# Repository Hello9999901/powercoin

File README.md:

# powercoin

Powercoin is an ultra-compact Qi-certified wireless power transfer receiver. A functional prototype was achieved in May 2022, and full integration into devices like the Logitech G502 or similar Razer products are planned. Optimized for production with JLCPCB.

> _Blender animated render of the powercoin (EEVEE rendering engine, custom procedural materials)_

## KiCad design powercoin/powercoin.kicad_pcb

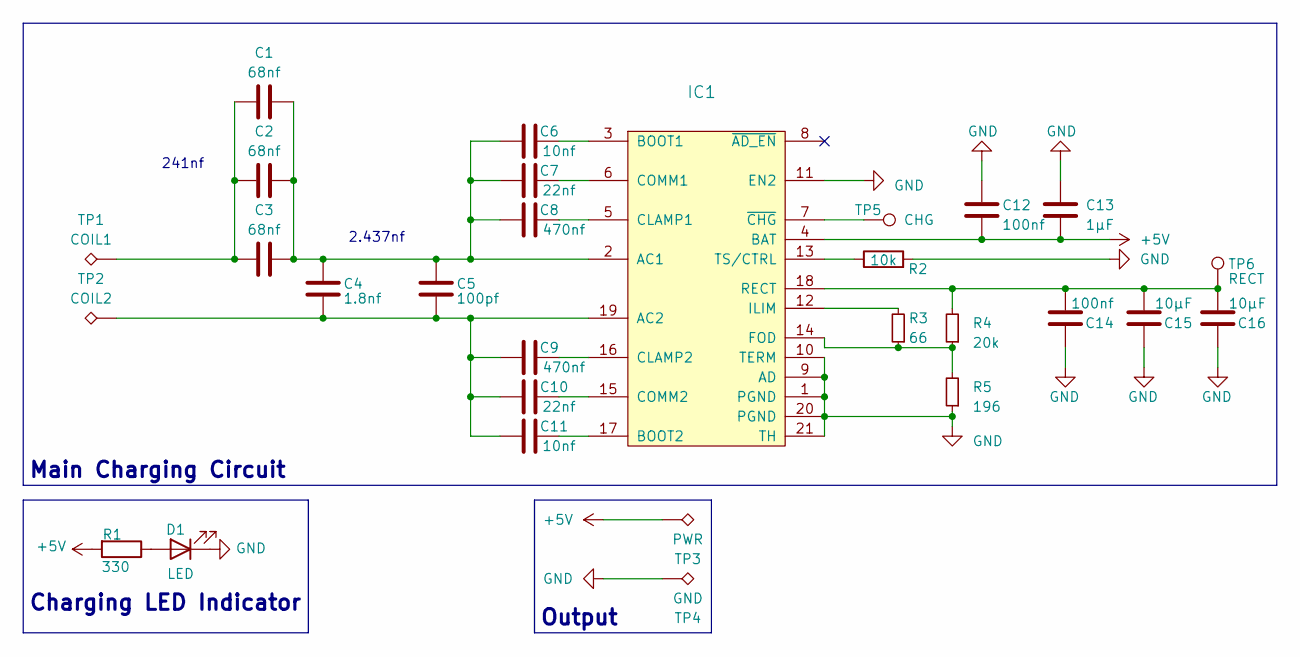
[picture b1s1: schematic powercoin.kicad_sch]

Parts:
C1, C2, C3: 68nf; C_0603_1608Metric; LCSC C107098
C4: 1.8nf; C_0603_1608Metric; LCSC C318642
C5: 100pf; C_0603_1608Metric; LCSC C14858
C6, C11: 10nf; C_0603_1608Metric; LCSC C100042
C7, C10: 22nf; C_0603_1608Metric; LCSC C21122
C8, C9: 470nf; C_0603_1608Metric; LCSC C1620
C12, C14: 100nf; C_0603_1608Metric; LCSC C14663
C13: 1μF; C_0603_1608Metric; LCSC C1592
C15, C16: 10μF; C_0603_1608Metric; LCSC C85713
D1: LED; LED_0805_2012Metric; LCSC C965818
IC1: Texas_VQFN-RHL-20; MPN BQ51050BRHLR; LCSC C55663
R1: 330; R_0603_1608Metric; LCSC C23138
R2: 10k; R_0603_1608Metric; LCSC C99198
R3: 66; R_0603_1608Metric; LCSC C245056
R4: 20k; R_0603_1608Metric; LCSC C4184
R5: 196; R_0603_1608Metric; LCSC C22899
TP1: COIL1; TestPoint_Keystone_5019_Minature
TP2: COIL2; TestPoint_Keystone_5019_Minature
TP3: PWR; TestPoint_Keystone_5019_Minature
TP4: GND; TestPoint_Keystone_5019_Minature
TP5: CHG; TestPoint_THTPad_D1.0mm_Drill0.5mm
TP6: RECT; TestPoint_THTPad_D1.0mm_Drill0.5mm

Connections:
+5V: C12.1, C13.1, IC1.4 (BAT), R1.2, TP3.1
GND: C12.2, C13.2, C14.2, C15.2, C16.2, D1.1 (K), IC1.1 (PGND), IC1.9 (AD), IC1.10 (TERM), IC1.11 (EN2), IC1.20 (PGND), IC1.21 (TH), R2.2, R5.1, TP4.1
unnamed: C1.1, C2.1, C3.1, TP1.1
unnamed: D1.2 (A), R1.1
unnamed: C1.2, C2.2, C3.2, C4.2, C5.2, C6.1, C7.1, C8.1, IC1.2 (AC1)
unnamed: C4.1, C5.1, C9.1, C10.1, C11.1, IC1.19 (AC2), TP2.1
unnamed: C6.2, IC1.3 (BOOT1)
unnamed: C11.2, IC1.17 (BOOT2)
unnamed: C8.2, IC1.5 (CLAMP1)
unnamed: C9.2, IC1.16 (CLAMP2)
unnamed: C7.2, IC1.6 (COMM1)
unnamed: C10.2, IC1.15 (COMM2)
unnamed: IC1.14 (FOD), R3.1, R4.1, R5.2
unnamed: IC1.12 (ILIM), R3.2
unnamed: C14.1, C15.1, C16.1, IC1.18 (RECT), R4.2, TP6.1
unnamed: IC1.13 (TS/CTRL), R2.1
unnamed: IC1.7 (~CHG), TP5.1

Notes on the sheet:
Output
2.437nf
Main Charging Circuit
241nf
Charging LED Indicator

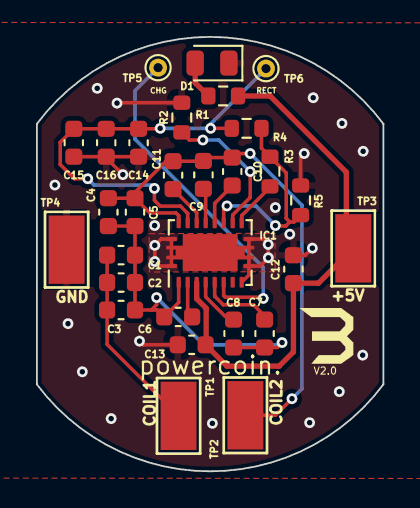
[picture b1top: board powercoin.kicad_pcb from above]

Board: 2 copper layers, 19.2 x 24.1 mm, 29 parts (0 on the bottom side), 17 nets.

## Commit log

2023-07-23 New: added powercoin project
2023-07-23 Feat: add render
